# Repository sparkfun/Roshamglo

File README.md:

SparkFun Roshamglo
=============================================
Giveaway rock, paper, scissors laser tag badge.

[*SparkFun Roshamglo (KIT-14130)*](https://www.sparkfun.com/products/14130)

The SparkFun Roshamglo is a badge that can be worn with a lanyard clip that has been designed to play Rock Paper Scissors. The board uses the ATtiny84, and has an IR LED and receiver to communicate between badges. To play, simply point the USB connector at your opponents controller up to 5 feet away and press the 5-way switch to the left for rock, up for paper, and right for scissors. The red/green LED will display a solid red for lose, green for win, or alternate red and green for a tie. The Roshamglo uses the [Micronucleaus](https://github.com/micronucleus/micronucleus) bootloader, which allows for USB programming from the Arduino IDE. 
 
 Repository Contents
-------------------
* **/Artwork** - Artwork for custom images (.svg)
* **/Bootloader** - Files needed to install the Micronucleaus bootloader
* **/Datasheets** - Datasheets for various components used (.pdf)
* **/Firmware** - Code used to play Rock Paper Scissors (.ino)
* **/Hardware** - All Eagle design files (.brd, .sch, .dxf, .lbr, .scr)

Documentation
--------------
* **[Hookup Guide](https://learn.sparkfun.com/tutorials/roshamglo-hookup-guide)** - Basic hookup guide.
* **[Roshamglo Project: TV-B-Gone](https://learn.sparkfun.com/tutorials/roshamglo-project-tv-b-gone)**
* **[Hack Your Roshamglo Badge](https://learn.sparkfun.com/tutorials/hack-your-roshamglo-badge)** 

License Information
-------------------
The hardware is released under [Creative Commons ShareAlike 4.0 International](https://creativecommons.org/licenses/by-sa/4.0/).
The code is beerware; if you see me (or any other SparkFun employee) at the local, and you've found our code helpful, please buy us a round!

Distributed as-is; no warranty is given.

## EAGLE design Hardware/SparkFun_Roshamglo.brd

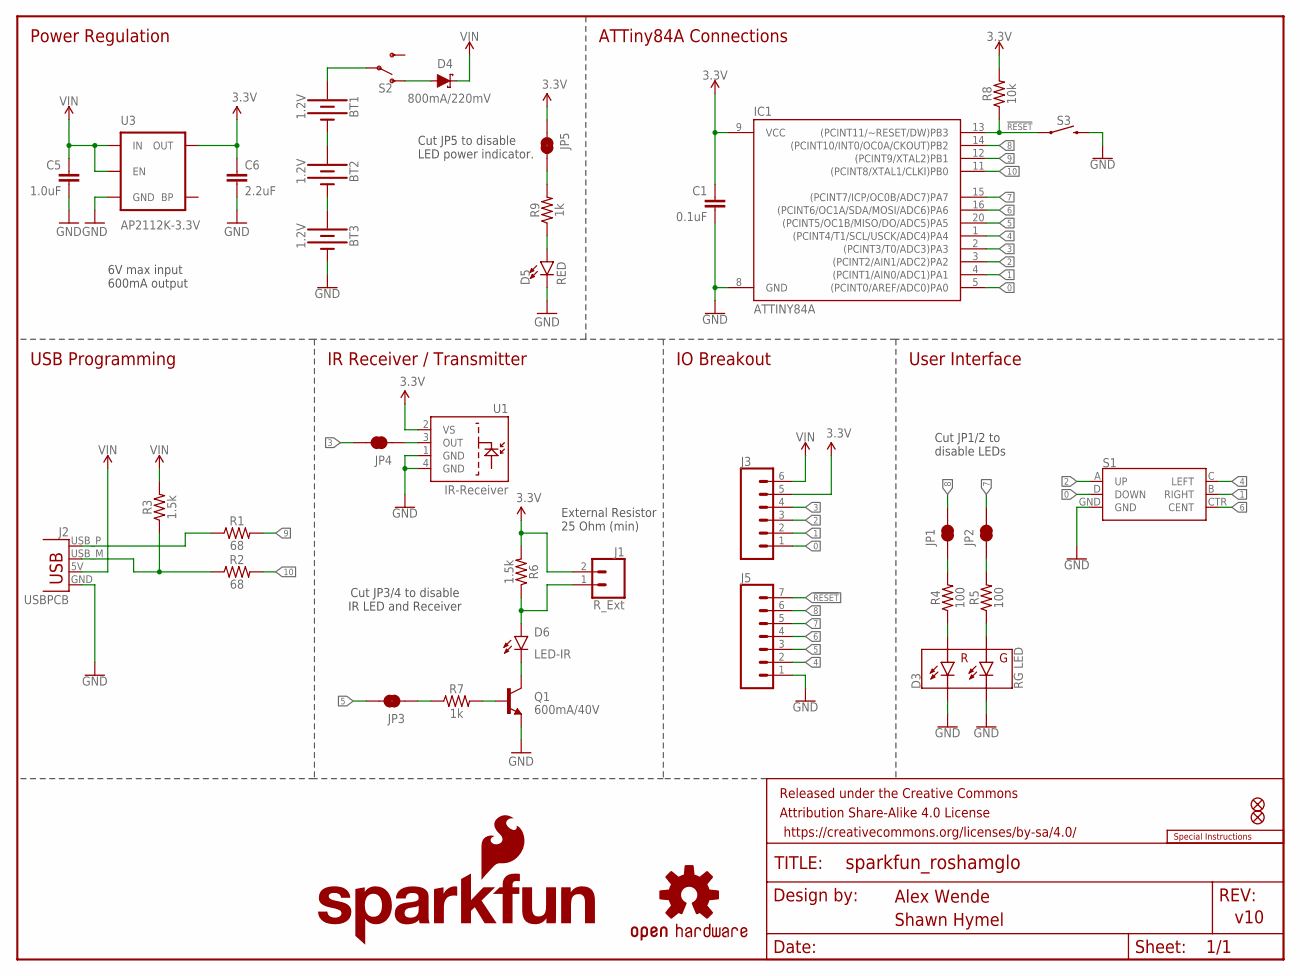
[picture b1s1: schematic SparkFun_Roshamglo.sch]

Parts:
BT1, BT2, BT3: 1.2V; BATTERY-AAA-KIT
C1: 0.1uF; 0603
C5: 1.0uF; 0805-CAP
C6: 2.2uF; 0603-CAP
D3: RG LED; LTST-C195KGJRKT
D4: 800mA/220mV; SOD-323
D5: RED; LED-0603
D6: LED-IR; SFH4045N
FD1, FD2: FIDUCIALUFIDUCIAL; FIDUCIAL-MICRO
FRAME1: FRAME-LETTER; CREATIVE_COMMONS
IC1: ATTINY84A; QFN20
J1: R_Ext; 1X02_NO_SILK
J2: USBPCB; USB-A-PCB-NOPASTE
J3: CONN_06NO_SILK_FEMALE_PTH; 1X06_NO_SILK
J5: CONN_07NO_SILK; 1X07_NO_SILK
JP1, JP2, JP3, JP4, JP5: JUMPER-SMT_2_NC_TRACE_SILK; SMT-JUMPER_2_NC_TRACE_SILK
LOGO1: OSHW-LOGOS; OSHW-LOGO-S
LOGO2: SFE_LOGO_NAME_FLAME.2_INCH; SFE_LOGO_NAME_FLAME_.2
Q1: 600mA/40V; SOT23-3
R1, R2: 68; 0603
R3, R6: 1.5k; 0603
R4, R5: 100; 0603
R7, R9: 1k; 0603
R8: 10k; 0603
S1: JOYSTICK_MINI
S2: SWITCH-SPDT-SMD-RIGHT-ANGLE; SWITCH_SPST_SMD_A
S3: MOMENTARY-SWITCH-SPST-SMD-4.6X2.8MM; TACTILE_SWITCH_SMD_4.6X2.8MM
U1: IR-Receiver; TSOP75XXXWTR
U3: AP2112K-3.3V; SOT23-5
U$5: SPECIAL_INSTRUCTIONS-ORDERING; ORDERING_INSTRUCTIONS

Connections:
0: IC1.5 ((PCINT0/AREF/ADC0)PA0), J3.1, S1.D (DOWN)
1: IC1.4 ((PCINT1/AIN0/ADC1)PA1), J3.2, S1.B (RIGHT)
2: IC1.3 ((PCINT2/AIN1/ADC2)PA2), J3.3, S1.A (UP)
3: IC1.2 ((PCINT3/T0/ADC3)PA3), J3.4, JP4.2
3.3V: C1.1, C6.1, IC1.9 (VCC), J1.2, J3.5, JP5.1, R6.2, R8.2, U1.2 (VS), U3.5 (OUT)
4: IC1.1 ((PCINT4/T1/SCL/USCK/ADC4)PA4), J5.2, S1.C (LEFT)
5: IC1.20 ((PCINT5/OC1B/MISO/DO/ADC5)PA5), J5.3, JP3.2
6: IC1.16 ((PCINT6/OC1A/SDA/MOSI/ADC6)PA6), J5.4, S1.CTR (CENT)
7: IC1.15 ((PCINT7/ICP/OC0B/ADC7)PA7), J5.5, JP2.2
8: IC1.14 ((PCINT10/INT0/OC0A/CKOUT)PB2), J5.6, JP1.2
9: IC1.12 ((PCINT9/XTAL2)PB1), R1.2
10: IC1.11 ((PCINT8/XTAL1/CLKI)PB0), R2.2
!RESET: IC1.13 ((PCINT11/~RESET/DW)PB3), J5.7, R8.1, S3.1, S3.2 (1)
D+: J2.USB_P (D+), R1.1
D-: J2.USB_M (D-), R2.1, R3.1
GND: BT3.GND@1 (-), C1.2, C5.2, C6.2, D3.P$3 (GC), D3.P$4 (RC), D5.C, IC1.8 (GND), J2.GND, J5.1, Q1.2 (E), S1.GND, S3.3 (2), S3.4 (2), U1.1 (GND), U1.4 (GND), U3.2 (GND)
unnamed: D5.A, R9.1
unnamed: D3.P$2 (RA), R4.1
unnamed: D4.A, S2.1 (O)
unnamed: D3.P$1 (GA), R5.1
unnamed: D6.1 (C), Q1.3 (C)
unnamed: Q1.1 (B), R7.2
unnamed: JP1.1, R4.2
unnamed: JP2.1, R5.2
unnamed: JP4.1, U1.3 (OUT)
unnamed: JP3.1, R7.1
unnamed: JP5.2, R9.2
unnamed: BT1.GND@1 (-), BT2.PWR@1 (+)
unnamed: BT2.GND@1 (-), BT3.PWR@1 (+)
unnamed: D6.2 (A), J1.1, R6.1
VIN: C5.1, D4.C, J2.5V (VBUS), J3.6, R3.2, U3.1 (IN), U3.3 (EN)
V_BATT: BT1.PWR@1 (+), S2.2

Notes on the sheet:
6V max input 600mA output
Power Regulation
USB Programming
ATTiny84A Connections
IR Receiver / Transmitter
User Interface
Alex Wende
Shawn Hymel
v10
IO Breakout
Cut JP1/2 to disable LEDs
Cut JP3/4 to disable IR LED and Receiver
External Resistor 25 Ohm (min)
Cut JP5 to disable LED power indicator.

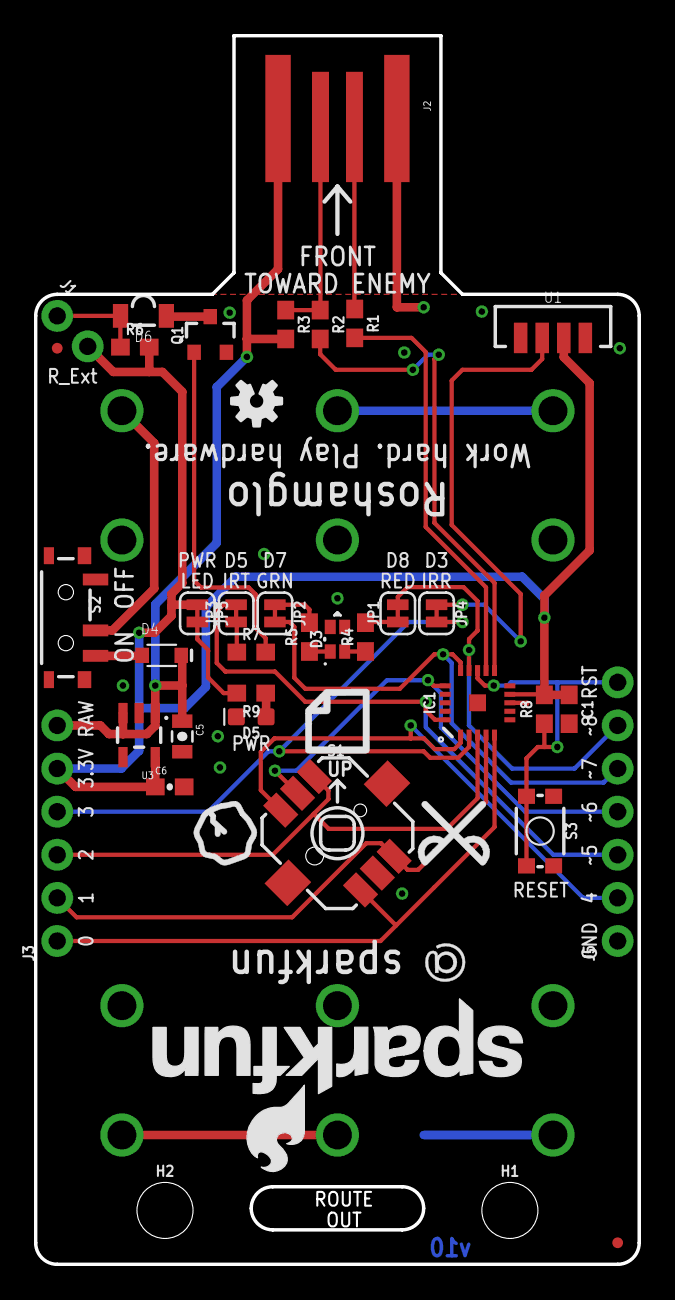
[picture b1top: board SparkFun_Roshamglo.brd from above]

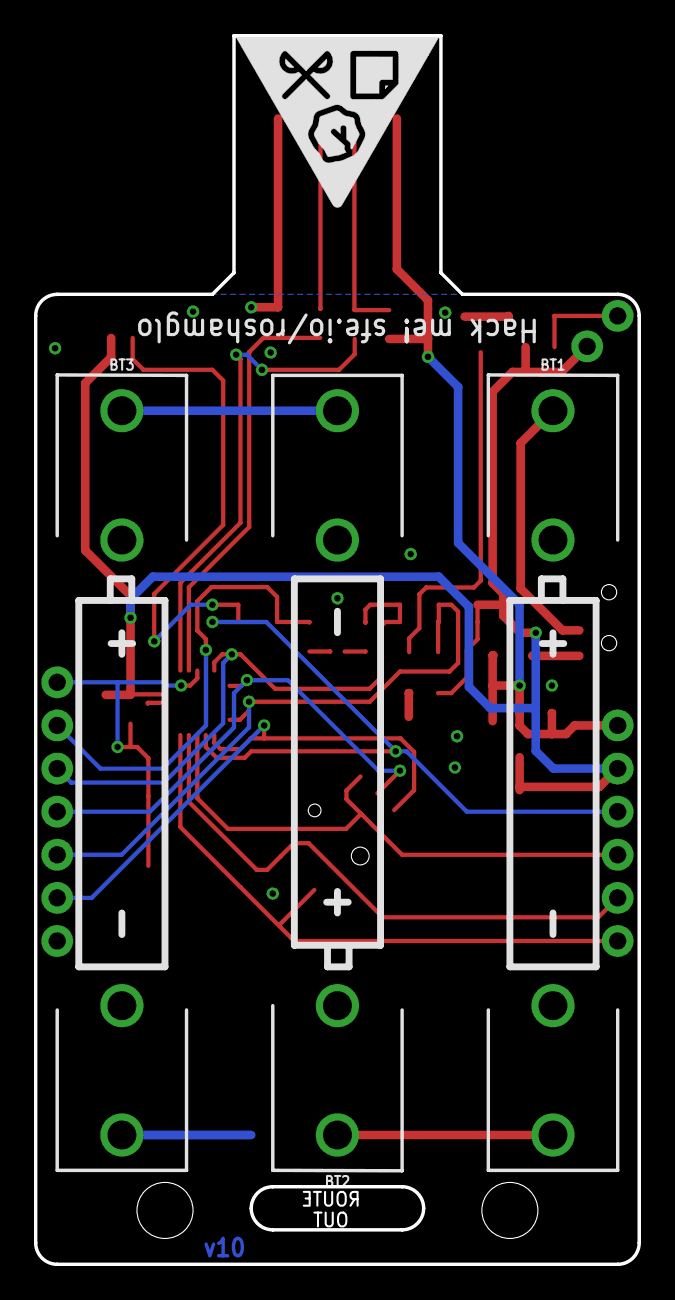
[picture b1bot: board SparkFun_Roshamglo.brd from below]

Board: 2 copper layers, 35.6 x 72.4 mm, 47 parts (4 on the bottom side), 32 nets.

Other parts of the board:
H1, H2: STAND-OFF
U$1: ROSHAMGLO_PAPER
U$2: ROSHAMGLO_ROCK
U$3: ROSHAMGLO_SCISSORS
U$4: ROSHAMGLO_LOGO_0.4

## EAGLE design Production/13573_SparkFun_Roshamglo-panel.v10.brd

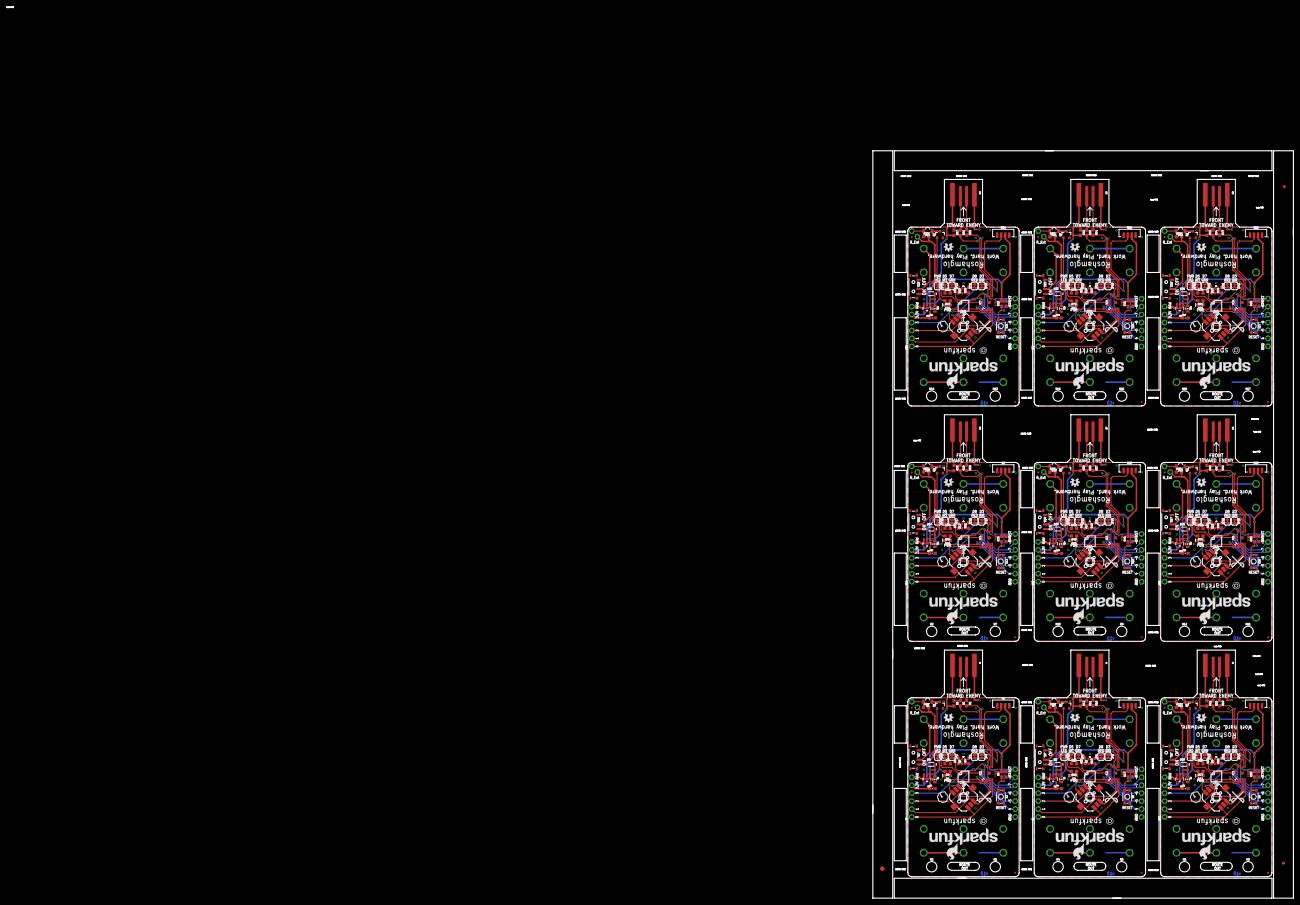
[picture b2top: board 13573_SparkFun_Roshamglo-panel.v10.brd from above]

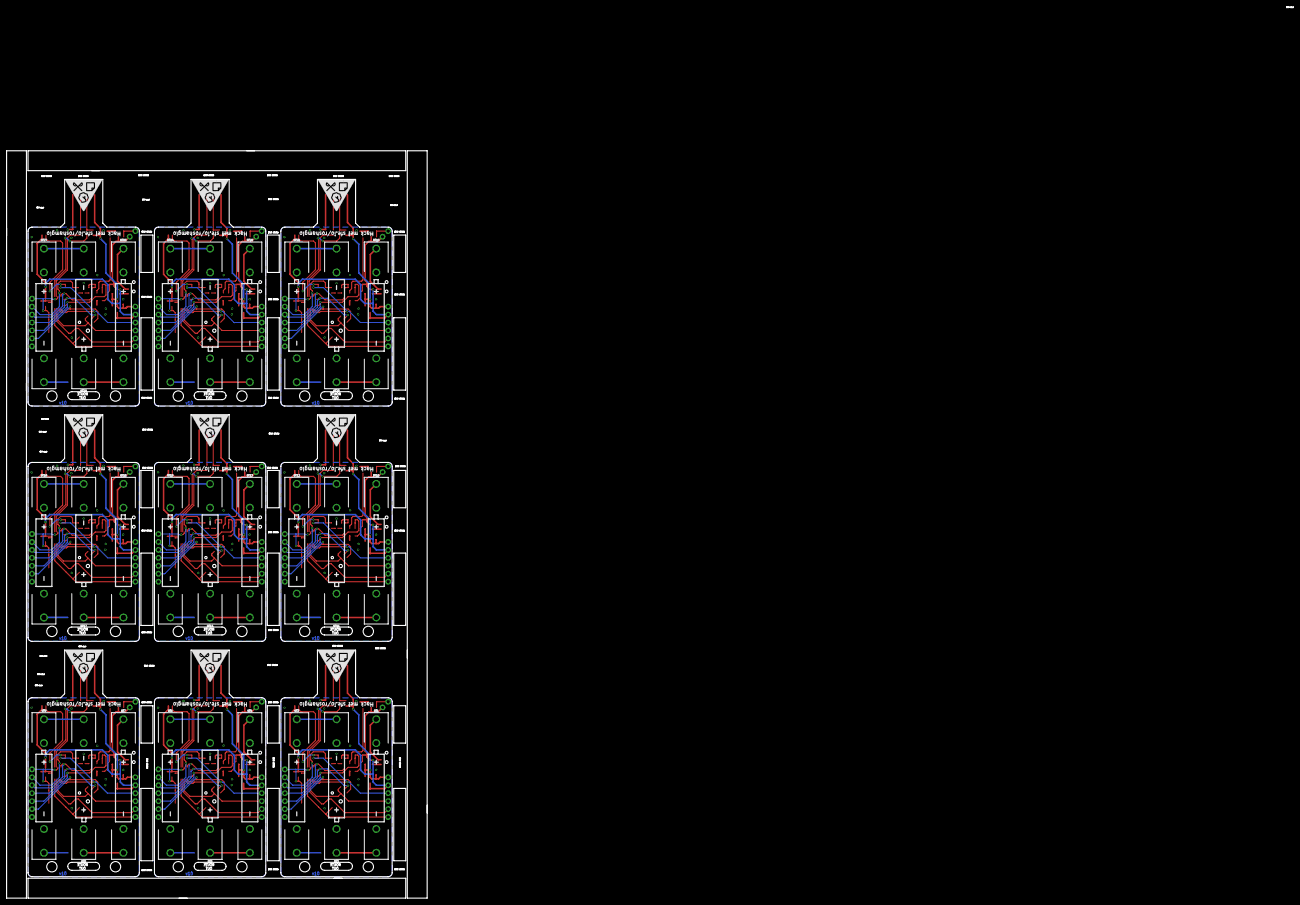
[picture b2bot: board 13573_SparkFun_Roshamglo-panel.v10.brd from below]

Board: 2 copper layers, 134.4 x 238.8 mm, 408 parts (36 on the bottom side), 288 nets.

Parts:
BT1, BT2, BT3, BT4, BT5, BT6, BT7, BT8, BT9, BT10, BT11, BT12, BT13, BT14, BT15, BT16, BT17, BT18, BT19, BT20, BT21, BT22, BT23, BT24, BT25, BT26, BT27: 1.2V; BATTERY-AAA-KIT
C1, C2, C7, C10, C13, C16, C19, C22, C25: 0.1uF; 0603
C3, C5, C8, C11, C14, C17, C20, C23, C26: 1.0uF; 0805-CAP
C4, C6, C9, C12, C15, C18, C21, C24, C27: 2.2uF; 0603-CAP
D1, D3, D9, D13, D17, D21, D25, D29, D33: RG LED; LTST-C195KGJRKT
D2, D4, D10, D14, D18, D22, D26, D30, D34: 800mA/220mV; SOD-323
D5, D8, D12, D16, D20, D24, D28, D32, D36: RED; LED-0603
D6, D7, D11, D15, D19, D23, D27, D31, D35: LED-IR; SFH4045N
E$1: FIDUCIAL-1.5X3
E$5, E$6: FIDUCIAL-1X2
FD1, FD2, FD3, FD4, FD5, FD6, FD7, FD8, FD9, FD10, FD11, FD12, FD13, FD14, FD15, FD16, FD17, FD18: FIDUCIALUFIDUCIAL; FIDUCIAL-MICRO
H1, H2, H3, H4, H5, H6, H7, H8, H9, H10, H11, H12, H13, H14, H15, H16, H17, H18: STAND-OFF
IC1, IC2, IC3, IC4, IC5, IC6, IC7, IC8, IC9: ATTINY84A; QFN20
J1, J7, J11, J15, J19, J23, J27, J31, J35: R_Ext; 1X02_NO_SILK
J2, J4, J9, J13, J17, J21, J25, J29, J33: USBPCB; USB-A-PCB-NOPASTE
J3, J8, J12, J16, J20, J24, J28, J32, J36: 1X06_NO_SILK
J5, J6, J10, J14, J18, J22, J26, J30, J34: 1X07_NO_SILK
JP1, JP2, JP3, JP4, JP5, JP6, JP7, JP8, JP9, JP10, JP11, JP12, JP13, JP14, JP15, JP16, JP17, JP18, JP19, JP20, JP21, JP22, JP23, JP24, JP25, JP26, JP27, JP28, JP29, JP30, JP31, JP32, JP33, JP34, JP35, JP36, JP37, JP38, JP39, JP40, JP41, JP42, JP43, JP44, JP45: SMT-JUMPER_2_NC_TRACE_SILK
LOGO1, LOGO3, LOGO5, LOGO7, LOGO9, LOGO11, LOGO13, LOGO15, LOGO17: OSHW-LOGOS; OSHW-LOGO-S
LOGO2, LOGO4, LOGO6, LOGO8, LOGO10, LOGO12, LOGO14, LOGO16, LOGO18: SFE_LOGO_NAME_FLAME.2_INCH; SFE_LOGO_NAME_FLAME_.2
Q1, Q2, Q3, Q4, Q5, Q6, Q7, Q8, Q9: 600mA/40V; SOT23-3
R1, R2, R10, R11, R19, R20, R28, R29, R37, R38, R46, R47, R55, R56, R64, R65, R73, R74: 68; 0603
R3, R6, R12, R15, R21, R24, R30, R33, R39, R42, R48, R51, R57, R60, R66, R69, R75, R78: 1.5k; 0603
R4, R5, R13, R14, R22, R23, R31, R32, R40, R41, R49, R50, R58, R59, R67, R68, R76, R77: 100; 0603
R7, R9, R16, R18, R25, R27, R34, R36, R43, R45, R52, R54, R61, R63, R70, R72, R79, R81: 1k; 0603
R8, R17, R26, R35, R44, R53, R62, R71, R80: 10k; 0603
S1, S4, S7, S10, S13, S16, S19, S22, S25: JOYSTICK_MINI
S2, S5, S8, S11, S14, S17, S20, S23, S26: SWITCH_SPST_SMD_A
S3, S6, S9, S12, S15, S18, S21, S24, S27: TACTILE_SWITCH_SMD_4.6X2.8MM
U1, U4, U6, U8, U10, U12, U14, U16, U18: IR-Receiver; TSOP75XXXWTR
U2, U3, U5, U7, U9, U11, U13, U15, U17: AP2112K-3.3V; SOT23-5
U$1, U$5, U$9, U$13, U$17, U$21, U$25, U$29, U$33: ROSHAMGLO_PAPER
U$2, U$6, U$10, U$14, U$18, U$22, U$26, U$30, U$34: ROSHAMGLO_ROCK
U$3, U$7, U$11, U$15, U$19, U$23, U$27, U$31, U$35: ROSHAMGLO_SCISSORS
U$4, U$8, U$12, U$16, U$20, U$24, U$28, U$32, U$36: ROSHAMGLO_LOGO_0.4

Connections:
0: IC1.5, J3.1, S1.D
1: IC1.4, J3.2, S1.B
2: IC1.3, J3.3, S1.A
3: IC1.2, J3.4, JP4.2
3.3V: C1.1, C6.1, IC1.9, J1.2, J3.5, JP5.1, R6.2, R8.2, U1.2, U3.5
3.3V1: C2.1, C4.1, IC2.9, J7.2, J8.5, JP10.1, R15.2, R17.2, U2.5, U4.2
3.3V2: C7.1, C9.1, IC3.9, J11.2, J12.5, JP15.1, R24.2, R26.2, U5.5, U6.2
3.3V3: C10.1, C12.1, IC4.9, J15.2, J16.5, JP20.1, R33.2, R35.2, U7.5, U8.2
3.3V4: C13.1, C15.1, IC5.9, J19.2, J20.5, JP25.1, R42.2, R44.2, U9.5, U10.2
3.3V5: C16.1, C18.1, IC6.9, J23.2, J24.5, JP30.1, R51.2, R53.2, U11.5, U12.2
3.3V6: C19.1, C21.1, IC7.9, J27.2, J28.5, JP35.1, R60.2, R62.2, U13.5, U14.2
3.3V7: C22.1, C24.1, IC8.9, J31.2, J32.5, JP40.1, R69.2, R71.2, U15.5, U16.2
3.3V8: C25.1, C27.1, IC9.9, J35.2, J36.5, JP45.1, R78.2, R80.2, U17.5, U18.2
4: IC1.1, J5.2, S1.C
5: IC1.20, J5.3, JP3.2
6: IC1.16, J5.4, S1.CTR
7: IC1.15, J5.5, JP2.2
8: IC1.14, J5.6, JP1.2
9: IC1.12, R1.2
10: IC1.11, R2.2
11: IC2.14, J6.6, JP6.2
12: IC2.12, R10.2
13: IC2.11, R11.2
14: IC2.15, J6.5, JP7.2
15: IC2.16, J6.4, S4.CTR
16: IC2.20, J6.3, JP8.2
17: IC2.1, J6.2, S4.C
18: IC2.2, J8.4, JP9.2
19: IC2.3, J8.3, S4.A
20: IC2.4, J8.2, S4.B
21: IC2.5, J8.1, S4.D
22: IC3.14, J10.6, JP11.2
23: IC3.12, R19.2
24: IC3.11, R20.2
25: IC3.15, J10.5, JP12.2
26: IC3.16, J10.4, S7.CTR
27: IC3.20, J10.3, JP13.2
28: IC3.1, J10.2, S7.C
29: IC3.2, J12.4, JP14.2
30: IC3.3, J12.3, S7.A
31: IC3.4, J12.2, S7.B
32: IC3.5, J12.1, S7.D
33: IC4.14, J14.6, JP16.2
34: IC4.12, R28.2
35: IC4.11, R29.2
36: IC4.15, J14.5, JP17.2
37: IC4.16, J14.4, S10.CTR
38: IC4.20, J14.3, JP18.2
39: IC4.1, J14.2, S10.C
40: IC4.2, J16.4, JP19.2
41: IC4.3, J16.3, S10.A
42: IC4.4, J16.2, S10.B
43: IC4.5, J16.1, S10.D
44: IC5.14, J18.6, JP21.2
45: IC5.12, R37.2
46: IC5.11, R38.2
47: IC5.15, J18.5, JP22.2
48: IC5.16, J18.4, S13.CTR
49: IC5.20, J18.3, JP23.2
50: IC5.1, J18.2, S13.C
51: IC5.2, J20.4, JP24.2
52: IC5.3, J20.3, S13.A
53: IC5.4, J20.2, S13.B
54: IC5.5, J20.1, S13.D
55: IC6.14, J22.6, JP26.2
56: IC6.12, R46.2
57: IC6.11, R47.2
58: IC6.15, J22.5, JP27.2
59: IC6.16, J22.4, S16.CTR
60: IC6.20, J22.3, JP28.2
61: IC6.1, J22.2, S16.C
62: IC6.2, J24.4, JP29.2
63: IC6.3, J24.3, S16.A
64: IC6.4, J24.2, S16.B
65: IC6.5, J24.1, S16.D
66: IC7.14, J26.6, JP31.2
67: IC7.12, R55.2
68: IC7.11, R56.2
69: IC7.15, J26.5, JP32.2
70: IC7.16, J26.4, S19.CTR
71: IC7.20, J26.3, JP33.2
72: IC7.1, J26.2, S19.C
73: IC7.2, J28.4, JP34.2
74: IC7.3, J28.3, S19.A
75: IC7.4, J28.2, S19.B
76: IC7.5, J28.1, S19.D
77: IC8.14, J30.6, JP36.2
78: IC8.12, R64.2
79: IC8.11, R65.2
80: IC8.15, J30.5, JP37.2
81: IC8.16, J30.4, S22.CTR
82: IC8.20, J30.3, JP38.2
83: IC8.1, J30.2, S22.C
84: IC8.2, J32.4, JP39.2
85: IC8.3, J32.3, S22.A
86: IC8.4, J32.2, S22.B
87: IC8.5, J32.1, S22.D
88: IC9.14, J34.6, JP41.2
89: IC9.12, R73.2
90: IC9.11, R74.2
91: IC9.15, J34.5, JP42.2
92: IC9.16, J34.4, S25.CTR
93: IC9.20, J34.3, JP43.2
94: IC9.1, J34.2, S25.C
95: IC9.2, J36.4, JP44.2
96: IC9.3, J36.3, S25.A
97: IC9.4, J36.2, S25.B
98: IC9.5, J36.1, S25.D
!RESET: IC1.13, J5.7, R8.1, S3.1, S3.2
!RESET1: IC2.13, J6.7, R17.1, S6.1, S6.2
!RESET2: IC3.13, J10.7, R26.1, S9.1, S9.2
!RESET3: IC4.13, J14.7, R35.1, S12.1, S12.2
!RESET4: IC5.13, J18.7, R44.1, S15.1, S15.2
!RESET5: IC6.13, J22.7, R53.1, S18.1, S18.2
!RESET6: IC7.13, J26.7, R62.1, S21.1, S21.2
!RESET7: IC8.13, J30.7, R71.1, S24.1, S24.2
!RESET8: IC9.13, J34.7, R80.1, S27.1, S27.2
D+: J2.USB_P, R1.1
D+1: J4.USB_P, R10.1
D+2: J9.USB_P, R19.1
D+3: J13.USB_P, R28.1
D+4: J17.USB_P, R37.1
D+5: J21.USB_P, R46.1
D+6: J25.USB_P, R55.1
D+7: J29.USB_P, R64.1
D+8: J33.USB_P, R73.1
D-: J2.USB_M, R2.1, R3.1
D-1: J4.USB_M, R11.1, R12.1
D-2: J9.USB_M, R20.1, R21.1
D-3: J13.USB_M, R29.1, R30.1
D-4: J17.USB_M, R38.1, R39.1
D-5: J21.USB_M, R47.1, R48.1
D-6: J25.USB_M, R56.1, R57.1
D-7: J29.USB_M, R65.1, R66.1
D-8: J33.USB_M, R74.1, R75.1
GND: BT3.GND@1, C1.2, C5.2, C6.2, D3.P$3, D3.P$4, D5.C, IC1.8, J2.GND, J5.1, Q1.2, S1.GND, S3.3, S3.4, U1.1, U1.4, U3.2
GND1: BT6.GND@1, C2.2, C3.2, C4.2, D1.P$3, D1.P$4, D8.C, IC2.8, J4.GND, J6.1, Q2.2, S4.GND, S6.3, S6.4, U2.2, U4.1, U4.4
GND2: BT9.GND@1, C7.2, C8.2, C9.2, D9.P$3, D9.P$4, D12.C, IC3.8, J9.GND, J10.1, Q3.2, S7.GND, S9.3, S9.4, U5.2, U6.1, U6.4
GND3: BT12.GND@1, C10.2, C11.2, C12.2, D13.P$3, D13.P$4, D16.C, IC4.8, J13.GND, J14.1, Q4.2, S10.GND, S12.3, S12.4, U7.2, U8.1, U8.4
GND4: BT15.GND@1, C13.2, C14.2, C15.2, D17.P$3, D17.P$4, D20.C, IC5.8, J17.GND, J18.1, Q5.2, S13.GND, S15.3, S15.4, U9.2, U10.1, U10.4
GND5: BT18.GND@1, C16.2, C17.2, C18.2, D21.P$3, D21.P$4, D24.C, IC6.8, J21.GND, J22.1, Q6.2, S16.GND, S18.3, S18.4, U11.2, U12.1, U12.4
GND6: BT21.GND@1, C19.2, C20.2, C21.2, D25.P$3, D25.P$4, D28.C, IC7.8, J25.GND, J26.1, Q7.2, S19.GND, S21.3, S21.4, U13.2, U14.1, U14.4
GND7: BT24.GND@1, C22.2, C23.2, C24.2, D29.P$3, D29.P$4, D32.C, IC8.8, J29.GND, J30.1, Q8.2, S22.GND, S24.3, S24.4, U15.2, U16.1, U16.4
GND8: BT27.GND@1, C25.2, C26.2, C27.2, D33.P$3, D33.P$4, D36.C, IC9.8, J33.GND, J34.1, Q9.2, S25.GND, S27.3, S27.4, U17.2, U18.1, U18.4
unnamed: D5.A, R9.1
unnamed: D3.P$2, R4.1
unnamed: D4.A, S2.1
unnamed: D3.P$1, R5.1
unnamed: D6.1, Q1.3
unnamed: Q1.1, R7.2
unnamed: JP1.1, R4.2
unnamed: JP2.1, R5.2
unnamed: JP4.1, U1.3
unnamed: JP3.1, R7.1
unnamed: JP5.2, R9.2
unnamed: BT1.GND@1, BT2.PWR@1
unnamed: BT2.GND@1, BT3.PWR@1
unnamed: D6.2, J1.1, R6.1
unnamed: D1.P$2, R13.1
unnamed: D1.P$1, R14.1
unnamed: BT4.GND@1, BT5.PWR@1
unnamed: BT5.GND@1, BT6.PWR@1
unnamed: D2.A, S5.1
unnamed: JP6.1, R13.2
unnamed: JP7.1, R14.2
unnamed: D7.1, Q2.3
unnamed: Q2.1, R16.2
unnamed: JP9.1, U4.3
unnamed: JP8.1, R16.1
unnamed: D7.2, J7.1, R15.1
unnamed: D8.A, R18.1
unnamed: JP10.2, R18.2
unnamed: D9.P$2, R22.1
unnamed: D9.P$1, R23.1
unnamed: BT7.GND@1, BT8.PWR@1
unnamed: BT8.GND@1, BT9.PWR@1
unnamed: D10.A, S8.1
unnamed: JP11.1, R22.2
unnamed: JP12.1, R23.2
unnamed: D11.1, Q3.3
unnamed: Q3.1, R25.2
unnamed: JP14.1, U6.3
unnamed: JP13.1, R25.1
unnamed: D11.2, J11.1, R24.1
unnamed: D12.A, R27.1
unnamed: JP15.2, R27.2
unnamed: D13.P$2, R31.1
unnamed: D13.P$1, R32.1
unnamed: BT10.GND@1, BT11.PWR@1
unnamed: BT11.GND@1, BT12.PWR@1
unnamed: D14.A, S11.1
unnamed: JP16.1, R31.2
unnamed: JP17.1, R32.2
unnamed: D15.1, Q4.3
unnamed: Q4.1, R34.2
unnamed: JP19.1, U8.3
unnamed: JP18.1, R34.1
unnamed: D15.2, J15.1, R33.1
unnamed: D16.A, R36.1
unnamed: JP20.2, R36.2
unnamed: D17.P$2, R40.1
unnamed: D17.P$1, R41.1
unnamed: BT13.GND@1, BT14.PWR@1
unnamed: BT14.GND@1, BT15.PWR@1
unnamed: D18.A, S14.1
unnamed: JP21.1, R40.2
unnamed: JP22.1, R41.2
unnamed: D19.1, Q5.3
unnamed: Q5.1, R43.2
unnamed: JP24.1, U10.3
unnamed: JP23.1, R43.1
unnamed: D19.2, J19.1, R42.1
unnamed: D20.A, R45.1
unnamed: JP25.2, R45.2
unnamed: D21.P$2, R49.1
unnamed: D21.P$1, R50.1
unnamed: BT16.GND@1, BT17.PWR@1
unnamed: BT17.GND@1, BT18.PWR@1
unnamed: D22.A, S17.1
unnamed: JP26.1, R49.2
unnamed: JP27.1, R50.2
unnamed: D23.1, Q6.3
unnamed: Q6.1, R52.2
unnamed: JP29.1, U12.3
unnamed: JP28.1, R52.1
unnamed: D23.2, J23.1, R51.1
unnamed: D24.A, R54.1
unnamed: JP30.2, R54.2
unnamed: D25.P$2, R58.1
unnamed: D25.P$1, R59.1
unnamed: BT19.GND@1, BT20.PWR@1
unnamed: BT20.GND@1, BT21.PWR@1
unnamed: D26.A, S20.1
unnamed: JP31.1, R58.2
unnamed: JP32.1, R59.2
unnamed: D27.1, Q7.3
unnamed: Q7.1, R61.2
unnamed: JP34.1, U14.3
unnamed: JP33.1, R61.1
unnamed: D27.2, J27.1, R60.1
unnamed: D28.A, R63.1
unnamed: JP35.2, R63.2
unnamed: D29.P$2, R67.1
unnamed: D29.P$1, R68.1
unnamed: BT22.GND@1, BT23.PWR@1
unnamed: BT23.GND@1, BT24.PWR@1
unnamed: D30.A, S23.1
unnamed: JP36.1, R67.2
unnamed: JP37.1, R68.2
unnamed: D31.1, Q8.3
unnamed: Q8.1, R70.2
unnamed: JP39.1, U16.3
unnamed: JP38.1, R70.1
unnamed: D31.2, J31.1, R69.1
unnamed: D32.A, R72.1
unnamed: JP40.2, R72.2
unnamed: D33.P$2, R76.1
unnamed: D33.P$1, R77.1
unnamed: BT25.GND@1, BT26.PWR@1
unnamed: BT26.GND@1, BT27.PWR@1
unnamed: D34.A, S26.1
unnamed: JP41.1, R76.2
unnamed: JP42.1, R77.2
unnamed: D35.1, Q9.3
unnamed: Q9.1, R79.2
unnamed: JP44.1, U18.3
unnamed: JP43.1, R79.1
unnamed: D35.2, J35.1, R78.1
unnamed: D36.A, R81.1
unnamed: JP45.2, R81.2
VIN: C5.1, D4.C, J2.5V, J3.6, R3.2, U3.1, U3.3
VIN1: C3.1, D2.C, J4.5V, J8.6, R12.2, U2.1, U2.3
VIN2: C8.1, D10.C, J9.5V, J12.6, R21.2, U5.1, U5.3
VIN3: C11.1, D14.C, J13.5V, J16.6, R30.2, U7.1, U7.3
VIN4: C14.1, D18.C, J17.5V, J20.6, R39.2, U9.1, U9.3
VIN5: C17.1, D22.C, J21.5V, J24.6, R48.2, U11.1, U11.3
VIN6: C20.1, D26.C, J25.5V, J28.6, R57.2, U13.1, U13.3
VIN7: C23.1, D30.C, J29.5V, J32.6, R66.2, U15.1, U15.3
VIN8: C26.1, D34.C, J33.5V, J36.6, R75.2, U17.1, U17.3
V_BATT: BT1.PWR@1, S2.2
V_BATT1: BT4.PWR@1, S5.2
V_BATT2: BT7.PWR@1, S8.2
V_BATT3: BT10.PWR@1, S11.2
V_BATT4: BT13.PWR@1, S14.2
V_BATT5: BT16.PWR@1, S17.2
V_BATT6: BT19.PWR@1, S20.2
V_BATT7: BT22.PWR@1, S23.2
V_BATT8: BT25.PWR@1, S26.2

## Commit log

2016-11-19 Added bootloader and Arduino board definition file
2016-11-28 Added datasheets
2016-11-28 Changed to SMD IR led and receiver in datasheets. Added IR receiver to local lib.
2016-11-28 Removed temp library filed
2016-11-28 Added IR LED symbol and footprint
2016-11-28 Added IR LED to library
2016-11-29 V01 Hardware
    - Initial Circuit Layout
    - Added Schottky diode to library
    - Added Prod_ID attributes for new parts
2016-11-29 Added version number to PCB
2016-11-29 V01 changes
    - Fixed version number DRC error
    - Added pin 1 marker to Attiny84 to make orientation obvious after
    placement.
2016-11-29 v01 changes
    - Extended USB connector length 0.1"
    - Added jumpers to pins 7 and 8
    - Changed project name silk to single word
    - Added PWM pin labels
    - Rotated pin names 90 deg
2016-11-30 v01 changes
    - Added labels to jumpers
    - Cleaned up a couple traces
2016-11-30 Fixed DRC Errors
2016-11-30 Design Review Changes
    - removed ISP
    - added 10k to reset pin
    - broke out reset pin
    - Moved components away from SS pins
    - Changed route out to dimmention layer
    - moved lanyard hole away from edge of board
2016-12-01 Fixed Battery t-stop and b-stop
2016-12-01 Added logos to local library
2016-12-01 Made RPS symbols larger. Added original artwork.
2016-12-01 Added logos
2016-12-01 Spun silk text to face the same way
2016-12-01 Fixed DRC error and added text for LEDs
2016-12-01 Added mock-up artwork
2016-12-01 Moved Roshamglo logo up and added fill silk to go off edge of USB connector
2016-12-01 Replaced transistor
2016-12-05 Fixed QC issues
    - Added RES-00824 to BOM
    - Added standoff measurments
    - Changed "ROUTE OUT" to dimention layer
2016-12-15 v02 Changes
    - Moved IR LED to GPIO 5
    - Moved red and green LEDs to GPIO 7 and 8
    - Moved IR receiver to GPIO 3
    - Moved center switch to GPIO 6
    - Increased distance between batteries
    - Increased board size to 1.4"
2016-12-15 Fixed V02 DRC errors
2016-12-17 Updated full logo in eagle lib.
2016-12-20 v02 changes
    Added power LED
    Added external parallel resistor
2016-12-20 v02 changes
    - Switch back to old size for lanyard clip
    - Changed the "@" to proportional
    - Moved pin 4 to other header to leave more room for battery terminal
    soldering
2016-12-20 Minor fixes
    Added ordering instructions to bottom of board
    Removed right angles in traces
2016-12-21 Adjusted lanyard clip size
    My change back in v02 wasn't quite what it was. Going back to 0.4" width
2016-12-21 Initial Firmware commit
    No where close to being complete, but usable.
2016-12-21 Updating code
    Game roughly works. The board still needs to be reset after each game
    though.
2017-01-06 Firmware changes
    - Introduced a random delay to minimize likelihood of transmitting at
    the same time.
    - Added EEPROM to store the board's ID, last opponent's ID, and number
    of times those boards have played each other.
2017-01-11 V10 changes
    - Removed zener diodes
    - Changed 33ohm IR LED resistor to 2.55k
    - Removed paste on USB conn
2017-01-12 v10 - replaced 2.55k resistor with 2.2k
2017-01-12 V1.0
    - Fixed some bugs
    - Decreased gameplay time
    - Added better random number generator
2017-01-12 Added @ symbol artwork to pcb
2017-01-12 Design Review changes
    Replaced some silk, and moved a via
2017-01-16 Firmware changes
    - Added escape option. To exit whatever mode you're in back to standby,
    press the keypad in any direction to abort and return to standby.
    - Added opponent ID tracking to hopefully ignore any IR code received
    after the first packet is read.
2017-01-17 Changed line width to 0.001 for custom artwork to prevent long CAM jobs.
2017-01-17 panel
2017-02-02 v1.2 Changes
    Updated ID to support 3-byte addresses
2017-02-16 Added UID generator in production folder
2017-02-21 Created README
2017-02-21 v1.3 Changes
    - Added sleep mode to save power during standby
    - Added self test code used in production testing
    - Replaced 2-byte ID with 3-byte ID
    - Added fading LED in standby mode to show the board is on and running
    - timerDelay function now takes the number of milliseconds to delay for
    instead of number * 32ms
2017-03-08 Added TV-B-Gone example
2017-03-08 Added pdf schematic
2017-03-31 Adding software
    Software for scoreboard
2017-03-31 Adding Arduino Source for Points Banks
2017-05-11 Added hex to int parsing in banks

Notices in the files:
parts and their libraries:
SparkFun-Batteries: Licensing: Creative Commons ShareAlike 4.0 International - https://creativecommons.org/licenses/by-sa/4.0
SparkFun-Aesthetics: Released under the Creative Commons Attribution Share-Alike 4.0 License
SparkFun-Aesthetics: Released under the Creative Commons
